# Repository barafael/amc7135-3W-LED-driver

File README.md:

# amc7135-3W-LED-driver

## Schematic

## PCB render

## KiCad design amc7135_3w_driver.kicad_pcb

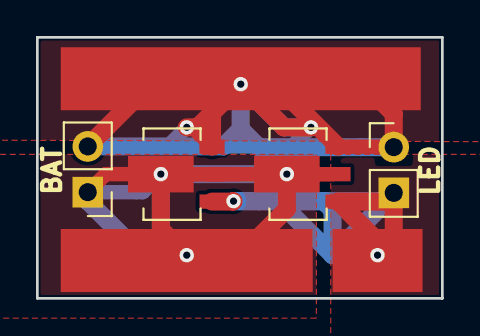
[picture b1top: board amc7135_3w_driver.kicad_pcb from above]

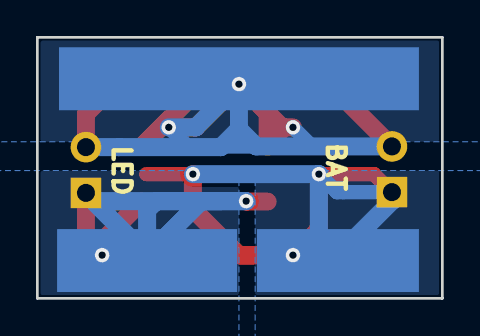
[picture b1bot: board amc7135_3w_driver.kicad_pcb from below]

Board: 2 copper layers, 22.5 x 14.5 mm, 10 parts (3 on the bottom side), 3 nets.

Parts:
J1: LED connector; PinHeader_1x02_P2.54mm_Vertical
J2: Power Connector; PinHeader_1x02_P2.54mm_Vertical
J3, J4, J5: heatsink; Pin_D1.0mm_L10.0mm_LooseFit
J3#2, J4#2, J5#2: Conn_01x01_Male; Pin_D1.0mm_L10.0mm_LooseFit
U1, U2: AMC7135_SOT89; SOT89

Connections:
GND: J2.1, J4.1, J4#2.1, U1.2, U2.2
unnamed: J1.2, J5.1, J5#2.1, U1.1, U2.1
VDD: J1.1, J2.2, J3.1, J3#2.1, U1.3, U2.3

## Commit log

2018-11-03 Add readme
2018-11-03 Add kicad files
2018-11-03 Clean up the schematic a little
2018-11-10 circuit images
